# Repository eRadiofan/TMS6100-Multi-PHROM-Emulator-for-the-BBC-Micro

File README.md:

# TMS6100 milti-PHROM

This project contains the PCB design and firmware for a TMS6100 emulator, accommodating the following PHROM images:

* Acorn PHROMA (News presenter Kenneth Kendall's voice, Acorn specific format), bank 15
* VM61002 - the PHROM fitted to Acorn computer speech kits sold in the USA (American male voice, indexed phrases), bank 0
* VM10004 - military radio phrases (American male voice, non-indexed phrases), bank 2
* VM71003 - talking clock (American female voice, indexed phrases), bank 4
* Star Wars arcade game prases - from firmware version 1.1 onwards, courtesy of [nmikstas on github](https://nmikstas.github.io/portfolio/swAudio/swAudio.html), who provided [a full dissassembly of the speech ROM](https://github.com/nmikstas/star-wars-arcade-audio/blob/master/Star_Wars_Sound_ROM.asm). Presented on bank 10.

There is also a build option in Firmware/Common/Inc/ROMdata.h to make the following selection:

* Acorn PHROMA (News presenter Kenneth Kendall's voice, Acorn specific format), bank 15
* CD2325a - TI-99/4A PHROM part 1, bank 0
* CD2326a - TI-99/4A PHROM part 2, bank 1
* VM71003 - talking clock (American female voice, indexed phrases), bank 4

Uncomment `#define PHROMS_TI99` and re-build the project. It is provided for experimentation, but the TI-99 phrases were intended for the TMS5200 and don't sound quite right on the TMS5220. To use this emulator in an actual TI-99 speech synthesizer module, pin 13 (CS) must be connected to ground (0V). Schematics for the module show this pin as being connected to +5V.

Content of the PHROMs are documented in the source files located in Firmware/Common/Src/ROMdata_*

The PCB has the footprint of a DIP-28 and is intended to be plugged into the IC98 socket on the BBC Micro model A/B motherboard.

It is a fully-featured implementation, providing indirect addressing and compatibility with other PHROMs connected to the same bus, provided they don't operate in the same address space (check the PHROM bank numbers).

The project is subdivided into multiple sections, stored in the following folders:

* PCB - The Kicad project for the PCB
* Firmware - The STM32CubeIDE project providing the firmware
* Scripts - Utilities for converting data
* BASIC2 - BBC BASIC programs for testing the multi-PHROM
* Images - Photos of the constructed PCB and installation

Each of these sections has their own README, providing more information.

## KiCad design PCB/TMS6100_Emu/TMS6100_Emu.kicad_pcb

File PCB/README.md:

# PCB

This PCB was designed using Kicad v9.06.

The STM32G051F8P6 MCU is well suited to this project, having 5V tolerant IO, 64K of flash storage and capable of running at 64MHz. STM32G031F8P6 and STM32C051F8P6 should work also.

The PCB has a placeholder for JLCPCB order number, select the correct options when ordering.

Folder AD2_Tests contains Digilent Waveforms workspace configurations for Analog Discovery 2 that were used to test basic read functionality before putting it into the micro.

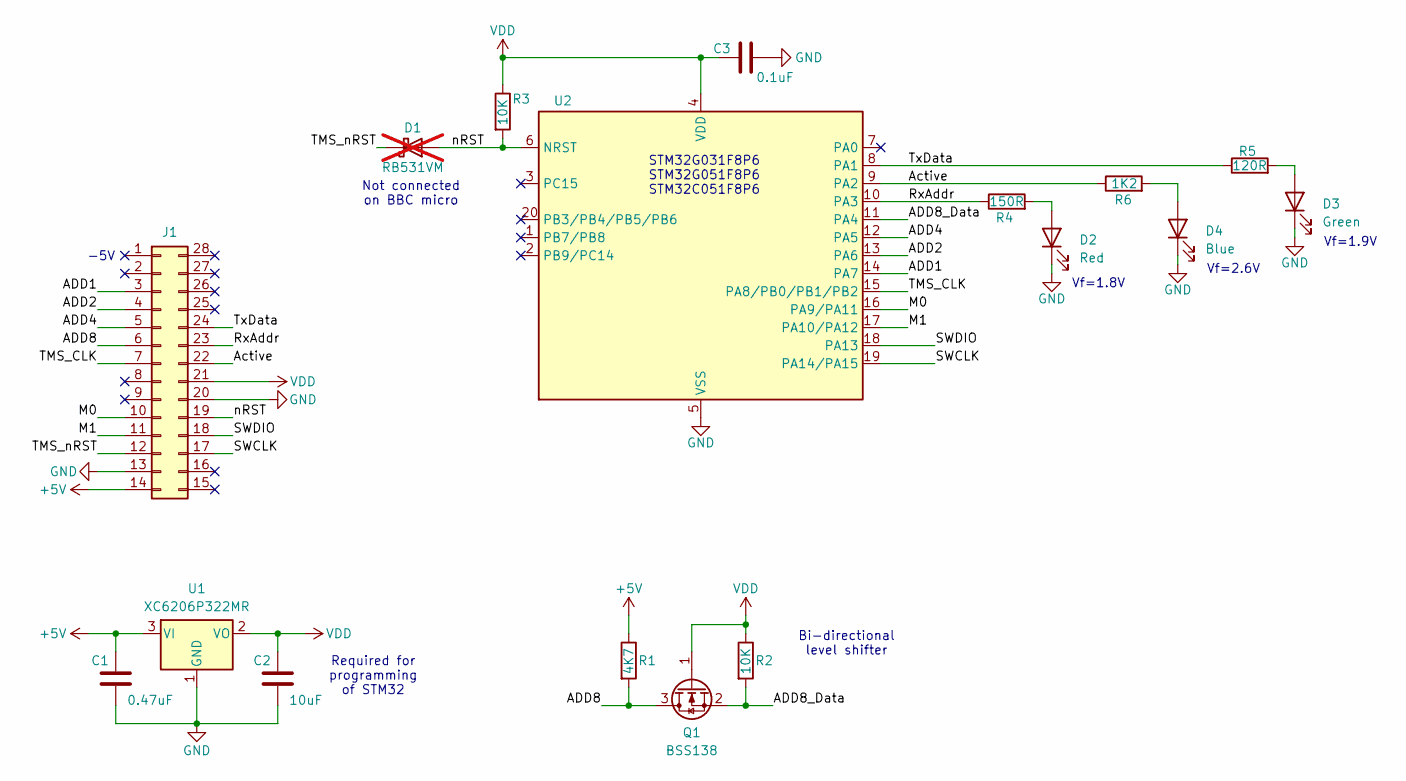
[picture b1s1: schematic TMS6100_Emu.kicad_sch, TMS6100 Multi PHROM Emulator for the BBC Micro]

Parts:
C1: 0.47uF; C_0805_2012Metric_Pad1.18x1.45mm_HandSolder
C2: 10uF; C_0805_2012Metric_Pad1.18x1.45mm_HandSolder
C3: 0.1uF; C_0603_1608Metric_Pad1.08x0.95mm_HandSolder
D1: RB531VM; D_SOD-323F; not fitted
D2: Red; LED_0805_2012Metric
D3: Green; LED_0805_2012Metric
D4: Blue; LED_0805_2012Metric
J1: Conn_02x14_Counter_Clockwise; DIP-28_W15.24mm_Socket
Q1: BSS138; SOT-23
R1: 4K7; R_0805_2012Metric_Pad1.20x1.40mm_HandSolder
R2, R3: 10K; R_0805_2012Metric_Pad1.20x1.40mm_HandSolder
R4: 150R; R_0805_2012Metric_Pad1.20x1.40mm_HandSolder
R5: 120R; R_0805_2012Metric_Pad1.20x1.40mm_HandSolder
R6: 1K2; R_0805_2012Metric_Pad1.20x1.40mm_HandSolder
U1: XC6206P322MR; SOT-23-3
U2: STM32G051F8P6; TSSOP-20_4.4x6.5mm_P0.65mm

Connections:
+5V: C1.1, J1.14, R1.1, U1.3 (VI)
/ADD1: J1.3, U2.14 (PA7)
/ADD2: J1.4, U2.13 (PA6)
/ADD4: J1.5, U2.12 (PA5)
/ADD8: J1.6, Q1.3 (D), R1.2
/ADD8_Data: Q1.2 (S), R2.2, U2.11 (PA4)
/Active: J1.22, R6.1, U2.9 (PA2)
/M0: J1.10, U2.16 (PA9/PA11)
/M1: J1.11, U2.17 (PA10/PA12)
/RxAddr: J1.23, R4.1, U2.10 (PA3)
/SWCLK: J1.17, U2.19 (PA14/PA15)
/SWDIO: J1.18, U2.18 (PA13)
/TMS_CLK: J1.7, U2.15 (PA8/PB0/PB1/PB2)
/TMS_nRST: D1.1 (K), J1.12
/TxData: J1.24, R5.1, U2.8 (PA1)
/nRST: D1.2 (A), J1.19, R3.2, U2.6 (NRST)
GND: C1.2, C2.2, C3.2, D2.1 (K), D3.1 (K), D4.1 (K), J1.13, J1.20, U1.1 (GND), U2.5 (VSS)
unnamed: D2.2 (A), R4.2
unnamed: D3.2 (A), R5.2
unnamed: D4.2 (A), R6.2
VDD: C2.1, C3.1, J1.21, Q1.1 (G), R2.1, R3.1, U1.2 (VO), U2.4 (VDD)

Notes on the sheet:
Vf=1.9V
STM32G031F8P6 STM32G051F8P6 STM32C051F8P6
Not connected on BBC micro
-5V
Vf=2.6V
Required for programming of STM32
Bi-directional level shifter
Vf=1.8V

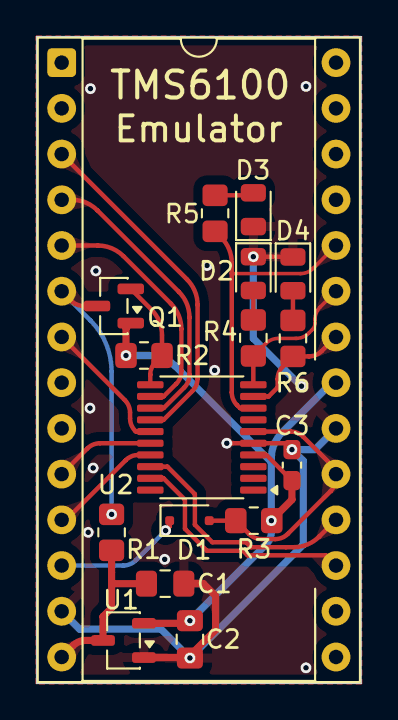
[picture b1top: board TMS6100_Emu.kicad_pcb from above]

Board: 2 copper layers, 18.0 x 35.9 mm, 17 parts (0 on the bottom side), 21 nets.

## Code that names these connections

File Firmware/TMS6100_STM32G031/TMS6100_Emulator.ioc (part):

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Mcu.Name=STM32G031F(4-6-8)Px
Mcu.Package=TSSOP20
Mcu.UserName=STM32G031F8Px
PA1.GPIOParameters=GPIO_Label
PA1.GPIO_Label=LED_Green
PA1.Signal=GPIO_Output
PA11\ [PA9].GPIOParameters=GPIO_Label
PA11\ [PA9].GPIO_Label=M0
PA11\ [PA9].Signal=GPXTI11
PA12\ [PA10].GPIOParameters=GPIO_Label
PA12\ [PA10].GPIO_Label=M1
PA12\ [PA10].Signal=GPXTI12
PA13.Mode=Serial_Wire
PA13.Signal=SYS_SWDIO
PA14-BOOT0.Mode=Serial_Wire
PA14-BOOT0.Signal=SYS_SWCLK
PA14-BOOT0__PA15.StandardMode=true
PA2.GPIOParameters=GPIO_Label
PA2.GPIO_Label=TP1
PA2.Signal=GPIO_Output
PA3.GPIOParameters=GPIO_Label
PA3.GPIO_Label=LED_Red
PA3.Signal=GPIO_Output
PA4.GPIOParameters=GPIO_Label
PA4.GPIO_Label=ADD8_Data
PA4.Signal=GPIO_Input
PA5.GPIOParameters=GPIO_Label
PA5.GPIO_Label=ADD4
PA5.Signal=GPIO_Input
PA6.GPIOParameters=GPIO_Label
PA6.GPIO_Label=ADD2
PA6.Signal=GPIO_Input
PA7.GPIOParameters=GPIO_Label
PA7.GPIO_Label=ADD1
PA7.Signal=GPIO_Input
PB0__PB1__PB2__PA8.StandardMode=true
PB2.GPIOParameters=GPIO_Label,GPIO_ModeDefaultEXTI
PB2.GPIO_Label=TMS_CLK
PB2.GPIO_ModeDefaultEXTI=GPIO_MODE_IT_FALLING
PB2.Signal=GPXTI2
PB3__PB4__PB5__PB6.StandardMode=true
PB7__PB8.StandardMode=true
PC14-OSC32_IN\ (PC14)__PB9.StandardMode=true
RCC.HSE_VALUE=8000000
RCC.SYSCLKFreq_VALUE=64000000
RCC.SYSCLKSource=RCC_SYSCLKSOURCE_PLLCLK
board=custom

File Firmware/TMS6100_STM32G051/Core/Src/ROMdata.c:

/*
 * ROMdata.c
 *
 *  Created: Jan 2026
 *   Author: Radiofan
 */
#include "main.h"
#include "stdbool.h"
#include "GPIO.h"
#include "ROMdata.h"

/* Measurements from BBC Micro:
 * M0 and M1 pulses are precisely 1 clock cycle in duration
 * M1 (address) pulses are on average 10 clock cycles apart
 *   and lag ADD8 setup by at least 1 clock cycle
 * M0 (read data) edges lag rising edge of clock signal by only 190ns
 * The gap between M0 pulses varies between 1 clock cycle and 350us,
 *   not necessarily aligned to word boundaries.
 * During indirect load M1 lags M0 by only 60ns, considered simultaneous
 */

/* Test scenarios to consider:
 *
 * 1) Reads from initial state should do nothing
 * 2) 5 address writes followed by reads should return the correct data
 * 3) Incomplete address writes followed by a read should reset to initial state
 * 4) 5 valid address writes followed by indirect read should return the correct data
 * 5) Indirect read from an unknown ROM address should reset to the initial unresponsive state
 * 6) Successive reads should continue incrementing the address
 * 7) Reading past end of ROM boundary (to next ROM) should return the correct data
 * 8) Reading past end of ROM boundary (to unknown ROM) should increment the address
 */

volatile uint8_t active = 0;

static volatile uint32_t currentAddress = 0;
static volatile const uint8_t *dataBank;
static volatile uint32_t phromSize;
static volatile uint32_t dataLength;

static volatile bool outputEnabled = false;
static volatile uint8_t outputByte;
static volatile uint8_t outputBitIndex;

static volatile rd_state readState = RD_INIT;
static volatile int8_t addrCount = 0;

static const int8_t PHROM_idx[16] = {1,-1,3,-1,2,-1,-1,-1,-1,-1,-1,-1,-1,-1,-1,0};
static const PHROM_desc PHROMs[N_PHROMS] = {
  { phromData_Acorn, 0x4000, DLEN_ACORN},
  { phromData_USA, 0x4000, DLEN_USA},
  { PHROMdata_Clock, 0x1000, DLEN_CLOCK},
  { PHROMdata_Mil, 0x4000, DLEN_Milit}
};

static inline void GPIO_Dout(void) {
  if (!outputEnabled) {
    GPIO_Init_Add8_D(GPIO_MODE_OUTPUT_OD);
    outputEnabled = true;
  }
}

static void GPIO_A8_in(void) {
  if (outputEnabled) {
    // Set the ADD8 bus pin to output mode and set the pin high
    // (as this is what the original TMS6100 does)
    GPIO_SetPin(GPIOA, ADD8_Data_Pin);
    GPIO_Init_Add8_D(GPIO_MODE_INPUT);
    outputEnabled = false;
  }
}

static void GPIO_A8_Out_Safe() {
  if (dataBank) {
    // Set the ADD8 bus pin to output mode
    GPIO_Dout();
  } else {
    // Set the ADD8 bus pin to input mode
    GPIO_A8_in();
  }
}

/* Most PHROMs are 16K in size, but the clock PHROM is only 4K.
 * Since some PHROMs use the last entry as a silent delay (series of zeros)
 * it is important to detect the end of the PHROM so that the delay can
 * stop in a timely manner. Releasing output on A8/D after the 4K boundary
 * results in 0xFF being read by the TMS5220, which stops speech.
 */

static void read_data_currentbank() {
  // Load the first byte to be sent (if this is our bank)
  if (dataBank) {
    uint32_t localAddress = (currentAddress & 0x3FFF);
    if (localAddress >= phromSize) {
      readState = RD_AOOB;
    } else {
      if (localAddress < dataLength) {
        outputByte = dataBank[localAddress];
      } else {
        // PHROMs are padded with 0s at the end
        outputByte = 0;
      }
      if (readState == RD_AOOB) {
        // Entering valid address space, enable data out
        readState = RD_READY;
        GPIO_A8_Out_Safe();
      }
    }
  } else {
    // No longer valid address. Note: switching A8 to input here
    //  would corrupt the last bit being sent
    readState = RD_AOOB;
  }
  // Reset the bit pointer
  outputBitIndex = 0;
}

static void read_data() {
  // Get the current bank and local address
  uint32_t currentBank = (currentAddress & 0x3C000) >> 14;
  int8_t i = PHROM_idx[currentBank];
  dataBank = NULL;
  if (i >= 0) {
      dataBank = PHROMs[i].address;
      phromSize = PHROMs[i].rom_size;
      dataLength = PHROMs[i].length;
  }
  // And read one byte
  read_data_currentbank();
}

static void M0_Dummy_Handler() {
  // This is the first M0 pulse after an M1 (address) pulse
  // Load the first byte to be sent (if from our bank)
  read_data();
  if (readState == RD_DUMMY) {
    readState = RD_READY;
    GPIO_A8_Out_Safe();
  }
}

static inline void M0_IncPointer() {
  // Increment the bit pointer
  if (++outputBitIndex == 8) {
    // Get the next byte to be sent
    currentAddress++;
    read_data();
  }
}

static inline void addr_reset() {
  addrCount = 0;
  readState = RD_INIT;
  currentAddress = 0;
}

static inline void M1_LoadAddress_Handler() {
  uint32_t addressNibble = 0;

  // Read the nibble from the address bus
  if (GPIO_ReadPin(GPIOA, ADD1_Pin)) addressNibble += 1;
  if (GPIO_ReadPin(GPIOA, ADD2_Pin)) addressNibble += 2;
  if (GPIO_ReadPin(GPIOA, ADD4_Pin)) addressNibble += 4;
  if (GPIO_ReadPin(GPIOA, ADD8_Data_Pin)) addressNibble += 8;

   // Shift the current address register right one nibble
   currentAddress = currentAddress >> 4;

   // Place the received nibble in the top of the current address register
   currentAddress |= (addressNibble << 16);

   if (++addrCount == 5) {
     addrCount = 0;
     readState = RD_DUMMY;
   } else
     readState = RD_ADDR;
}

static inline void M1_Indirect_Handler() {
  if (readState == RD_DUMMY) {
    // Address is complete, read the next two bytes as the next address
    read_data();
    if (readState == RD_DUMMY) {
      uint32_t locaAddress = (currentAddress & 0x3C000) | outputByte;
      currentAddress++;
      read_data_currentbank();
      currentAddress = locaAddress | ((outputByte & 0b00111111) << 8);
      if (readState == RD_DUMMY)
        M0_Dummy_Handler();
    } else {
      // Bad indirect address, reset
      readState = RD_INIT;
    }
  }
}

/* Actions are initiated on the rising edge of M0 and M1 but some operations
 * are only ready to complete on the next falling edge of the clock. The
 * rising edge handler sets a pending action in the tms_command variable,
 * the clock falling edge handler then carries out the action.
 */
#define TMS_NONE 0
#define TMS_M0_DUMMY 1
#define TMS_M1_ADDR  2
#define TMS_M0_INCP  4

static volatile uint8_t tms_command = 0;

/* M0_READ / M1_ADDR handler, must complete within 3.125uS (100 clock cycles at 32MHz)
 * ISR compiles to 85 instructions, should be OK
 */
void EXTI4_15_IRQHandler(void) {
  if (__HAL_GPIO_EXTI_GET_RISING_IT(M1_Pin) != 0x00u) {
    __HAL_GPIO_EXTI_CLEAR_RISING_IT(M1_Pin);
    GPIO_SetPin(GPIOA, LED_Red_Pin);
    // Make sure the ADD8 bus pin is in input mode
    GPIO_A8_in();
    // Read address on next falling edge of clock
    tms_command |= TMS_M1_ADDR;
    active = 1;
  }

  if (__HAL_GPIO_EXTI_GET_RISING_IT(M0_Pin) != 0x00u) {
    __HAL_GPIO_EXTI_CLEAR_RISING_IT(M0_Pin);
    if (readState == RD_DUMMY) {
      GPIO_SetPin(GPIOA, LED_Green_Pin);
      // Dummy read on next falling edge of clock
      tms_command |= TMS_M0_DUMMY;
    } else if (readState == RD_READY) {
      /* This is a bit read M0 pulse, data must be ready by the next
       * falling edge of clock, so we send it immediately...
       */
      GPIO_SetPin(GPIOA, LED_Green_Pin);
      // Push data to the output pin
      if (outputByte & (1 << outputBitIndex)) {
        GPIO_SetPin(GPIOA, ADD8_Data_Pin);
      } else {
        GPIO_ClrPin(GPIOA, ADD8_Data_Pin);
      }
      // Increment bit pointer on next falling edge of clock
      tms_command = TMS_M0_INCP;
    } else if (readState == RD_AOOB) {
      GPIO_A8_in();
      GPIO_SetPin(GPIOA, LED_Green_Pin);
      // Keep incrementing, in case we reach a valid ROM address
      tms_command |= TMS_M0_INCP;
    } else {
      // Bad address, reset
      addr_reset();
    }
    active = 1;
  }
}

/* ISR to handle falling edge of clock
 * We execute commands, inputs should be stable at this point.
 * Must complete within 3.125uS (100 clock cycles at 32MHz)
 * Compiles to 122 instructions but only one part of it
 *  is executed during each invocation.
 */
void EXTI2_3_IRQHandler(void) {
  if (__HAL_GPIO_EXTI_GET_RISING_IT(TMS_CLK_Pin) != 0x00u)
    __HAL_GPIO_EXTI_CLEAR_RISING_IT(TMS_CLK_Pin);

  if (__HAL_GPIO_EXTI_GET_FALLING_IT(TMS_CLK_Pin) != 0x00u) {
    __HAL_GPIO_EXTI_CLEAR_FALLING_IT(TMS_CLK_Pin);
    if (tms_command == TMS_M0_DUMMY) {
      M0_Dummy_Handler();
    } else if (tms_command == TMS_M1_ADDR) {
      M1_LoadAddress_Handler();
    } else if (tms_command == TMS_M0_INCP) {
      M0_IncPointer();
    } else if (tms_command == (TMS_M0_DUMMY | TMS_M1_ADDR)) {
      M1_Indirect_Handler();
    } else if (tms_command == (TMS_M0_INCP | TMS_M1_ADDR)) {
      // Bad indirect address, reset
      readState = RD_INIT;
    } else {
      GPIO_ClrPin(GPIOA, LED_Green_Pin);
      GPIO_ClrPin(GPIOA, LED_Red_Pin);
    }
    tms_command = TMS_NONE;
  }
}

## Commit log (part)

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2026-01-13 Initial commit, content merged from other repositories
2026-01-14 Added initial READMEs and photos of V1 PCB
2026-01-14 Update some READMEs
2026-01-14 Added schematic to README
2026-01-15 Phrase program can now speak all the phrases in sequence
2026-01-16 Added STM32G031 project and searated out the common code
2026-01-21 Added TI-99 phrase ROMs and the option to build them in
2026-01-22 Updated READMEs and Basic program to detect the TI-99 build option.
2026-01-27 Minor fix to Basic program, adjust blue LED resistor value
2026-01-30 Fix another bugette in the BASIC program
2026-02-03 Added Star Wars arcade game speech as bank 10
2026-02-11 BASIC: improve gap beween phrases, TI99 PHROM b-tree index now decoded, updated READMEs and a small optimisation switching ADD8.
2026-02-11 Small bugette in README
2026-03-01 StarWars fits into TI99 build opt, fixed TI99 PB, better frame debug
2026-03-08 Added TMS5220 clock speed utilirt

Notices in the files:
PCB/TMS6100_Emu/TMS6100_Emu.kicad_pcb:
©Radiofan
